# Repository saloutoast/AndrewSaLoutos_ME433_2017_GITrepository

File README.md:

Andrew SaLoutos, 3/28/2017

This repository contains my assignments and project progress for the ME 433 course.

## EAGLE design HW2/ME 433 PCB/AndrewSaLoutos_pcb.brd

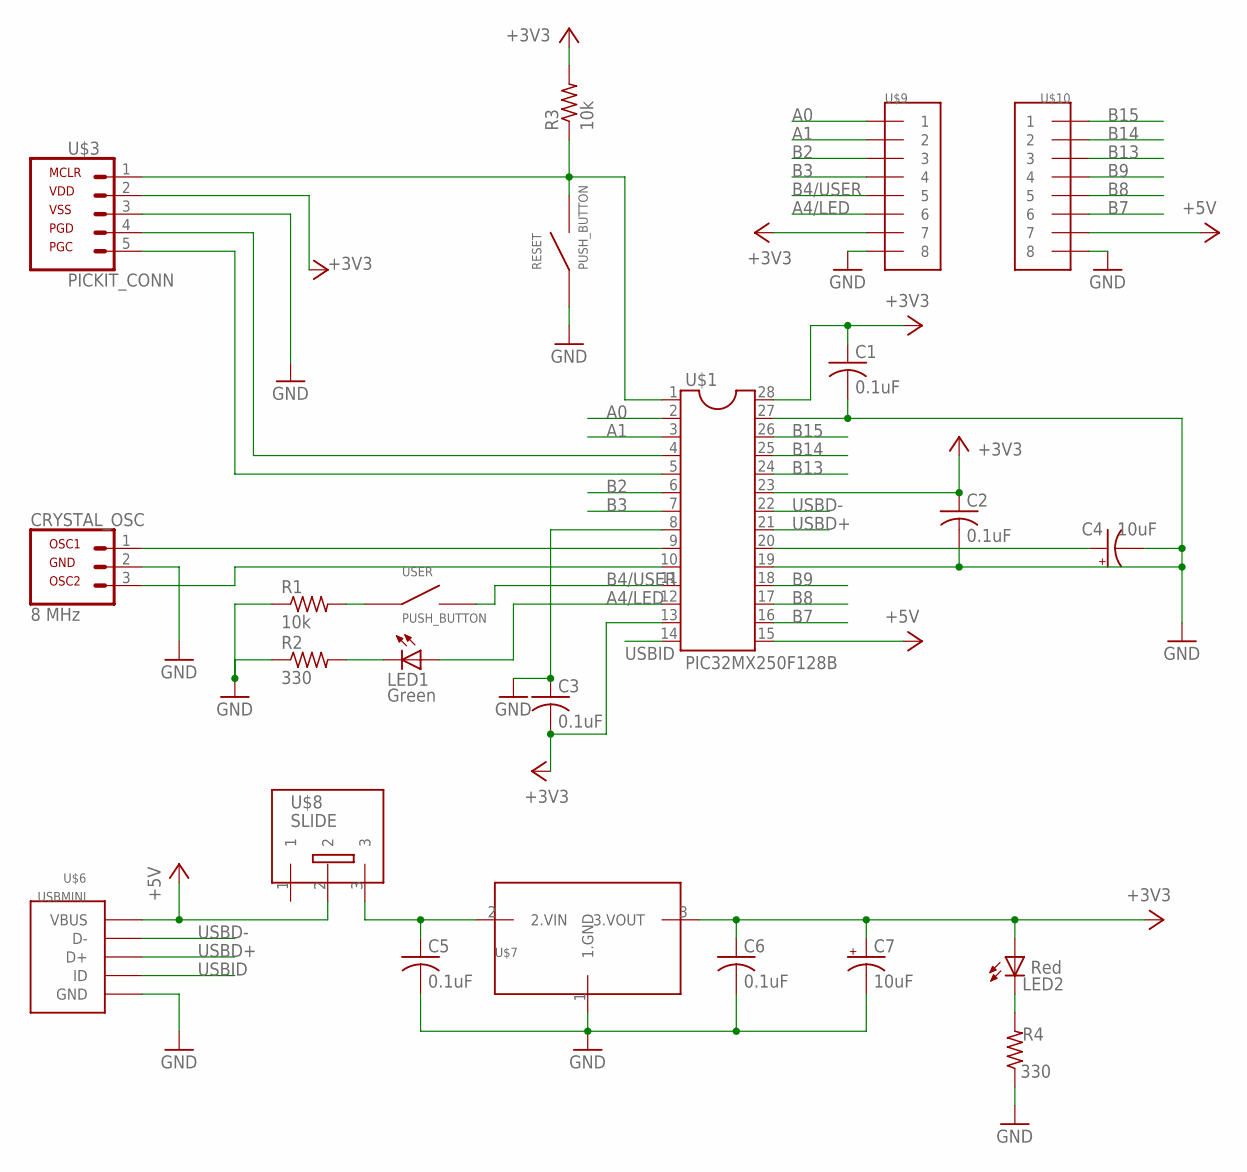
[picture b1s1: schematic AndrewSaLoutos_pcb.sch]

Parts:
C1, C2, C3, C5, C6: 0.1uF; C050-030X075
C4, C7: 10uF; E2,5-6
CRYSTAL_OSC: 8 MHz; 1X03
LED1: Green; LED3MM
LED2: Red; LED3MM
R1, R3: 10k; 0207/10
R2, R4: 330; 0207/10
RESET: PUSH_BUTTON
U$1: PIC32MX250F128B; DIL28-3
U$3: PICKIT_CONN; 1X05
U$6: USBMINI; USB-MB-H
U$7: MCP1702; TO92
U$8: SLIDE
U$9, U$10: 8PIN_HEADER
USER: PUSH_BUTTON

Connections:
+3V3: C1.1, C2.1, C3.2, C6.1, C7.+, LED2.A, R3.2, U$1.13 (13.VDD), U$1.23 (23.VUSB3.3), U$1.28 (28.AVDD), U$3.2 (2.VDD), U$7.3 (3.VOUT), U$9.7
+5V: U$1.15 (15.VBUS), U$6.VBUS, U$8.2, U$10.7
A0: U$1.2, U$9.1
A1: U$1.3, U$9.2
A4/LED: LED1.A, U$1.12 (12.RA4), U$9.6
B2: U$1.6, U$9.3
B3: U$1.7, U$9.4
B4/USER: U$1.11 (11.RB4), U$9.5, USER.3 (OUT)
B7: U$1.16, U$10.6
B8: U$1.17, U$10.5
B9: U$1.18, U$10.4
B13: U$1.24, U$10.3
B14: U$1.25, U$10.2
B15: U$1.26, U$10.1
GND: C1.2, C2.2, C3.1, C4.-, C5.2, C6.2, C7.-, CRYSTAL_OSC.2 (2.GND), R1.1, R2.1, R4.1, RESET.1 (IN), U$1.8 (8.VSS), U$1.19 (19.VSS), U$1.27 (27.AVSS), U$3.3 (3.VSS), U$6.GND, U$7.1 (1.GND), U$9.8, U$10.8
unnamed: C4.+, U$1.20 (20.VCAP)
unnamed: CRYSTAL_OSC.1 (1.OSC1), U$1.9 (9.OSC1)
unnamed: CRYSTAL_OSC.3 (3.OSC2), U$1.10 (10.OSC2)
unnamed: R1.2, USER.1 (IN)
unnamed: LED1.K (C), R2.2
unnamed: U$1.5 (5.PGEC1), U$3.5 (5.PGC)
unnamed: U$1.4 (4.PGED1), U$3.4 (4.PGD)
unnamed: R3.1, RESET.3 (OUT), U$1.1 (1.MCLR), U$3.1 (1.MCLR)
unnamed: C5.1, U$7.2 (2.VIN), U$8.3
unnamed: LED2.K (C), R4.2
USBD+: U$1.21, U$6.D+
USBD-: U$1.22, U$6.D-
USBID: U$1.14, U$6.ID

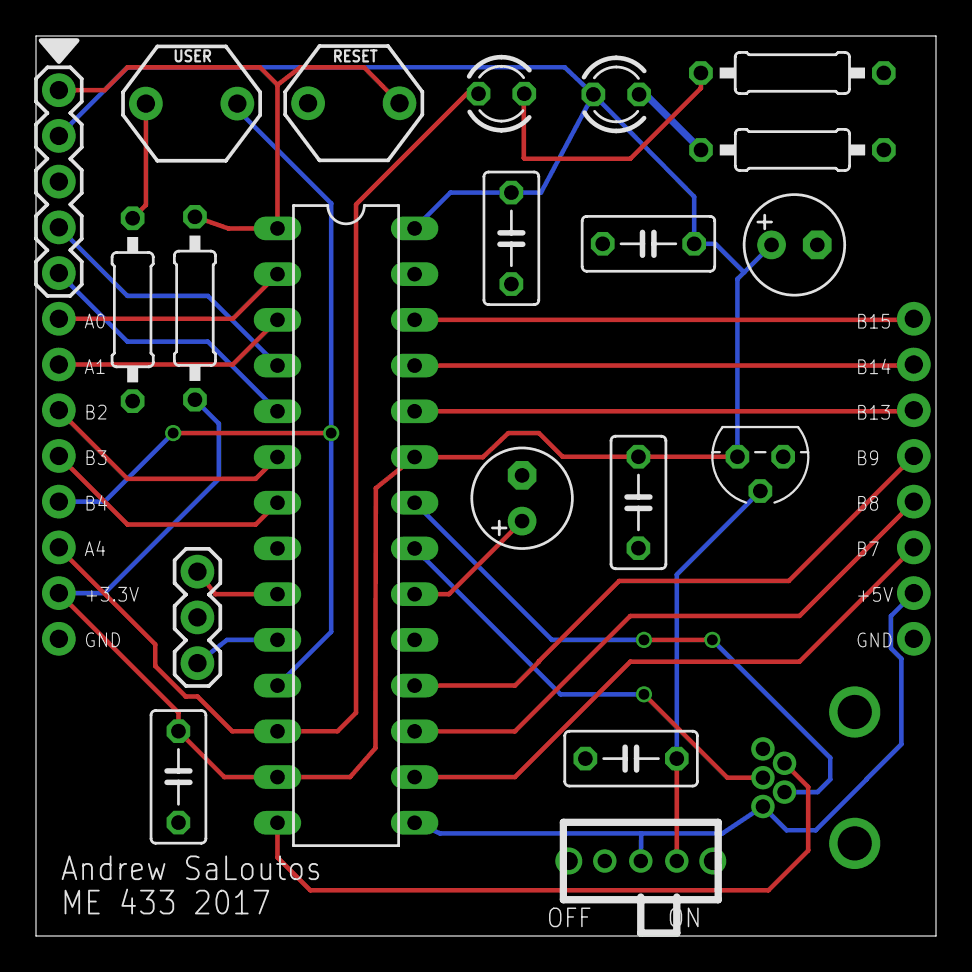
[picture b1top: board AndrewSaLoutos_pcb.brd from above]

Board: 2 copper layers, 50.0 x 50.0 mm, 23 parts (0 on the bottom side), 28 nets.

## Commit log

2017-03-28 My first commit!
2017-03-28 Added one line
2017-03-29 Built the voltage regulator circuit
2017-03-29 Complete circuit diagram
2017-03-29 Complete circuit
2017-03-29 Start of coding for HW1
2017-03-29 pragma values completed
2017-03-29 Toggle green LED, first attempt
2017-03-29 Toggle green LED, second attempt
2017-03-29 Just turn on green LED from PIC
2017-03-29 Toggle green LED, third attempt
2017-03-29 Successful toggle green LED at 50% at ~1 kHz
2017-03-29 push button pause, first attempt
2017-03-29 push button pause, second attempt
2017-03-29 Successful push button pause and restart LED toggling
2017-03-29 Push button and 1 kHz square wave demo video
2017-03-30 Started PCB design, finished creating the library
2017-04-03 Finished the schematic, started the board
2017-04-04 Actually, not quite done with the schematic
2017-04-04 Actually finished schematic, started board layout
2017-04-04 Making progress on board layout
2017-04-04 Everything on the board, not very neat yet
2017-04-04 Ground plane
2017-04-04 Started traces
2017-04-04 More traces
2017-04-04 Traces finished
2017-04-04 DRC checked with Seeed dru from master repository
2017-04-05 Finished board layout, added silkscreen text
2017-04-05 Rotated LED
2017-04-05 Gerber files generated and checked with Mayhew website, HW3 folder created
2017-04-05 Copied board file to HW3 folder
2017-04-10 Started HW4 code with SPI library
2017-04-10 Ready to test spi library
2017-04-10 While loop to test setVoltage function
2017-04-10 Deleted library attempt, square wave from DAC
2017-04-10 Debugging triangle wave, sine wave
2017-04-10 Triangle wave is still buggy, sine does not work
    Triangle wave from output A does not go above half voltage, output from
    B will only do triangle without trouble...it will not even stay high or
    low...will investigate the setVoltage function further tomorrow
2017-04-10 Triangle wave works on both Vout pins from DAC
2017-04-10 sin_track loop tested
2017-04-10 10 Hz sine, 5 Hz triangle outputs work
2017-04-10 Pictures of scope, circuit diagram for HW4
2017-04-11 Demo video
2017-04-12 Started HW5, copied I2C functions from github
2017-04-12 Added semicolon
2017-04-12 Added library for expander functions
2017-04-12 Working on expander functions
2017-04-12 Completed initExpander function
2017-04-12 Finished expander library
2017-04-13 Testing code
2017-04-13 LED blinking successfully when button is pressed
2017-04-13 Demo vid and circuit diagram
2017-04-14 Started HW6 project
2017-04-14 LCD library
2017-04-14 Started main function
2017-04-14 Starting char, string, bar functions
2017-04-14 Tested communication with screen
2017-04-14 Testing displaying one char
2017-04-14 Testing function
2017-04-14 Bar and string functions work
2017-04-14 Final code
2017-04-14 Now the code is final
2017-04-14 Circuit diagram and demo vid
2017-04-20 Testing communication with IMU
2017-04-20 who am i test succeeded
2017-04-20 Bars work, after making array unsigned
2017-04-20 Code complete
2017-04-21 need to remove spaces from file paths for harmony to compile
2017-04-22 Reinstalled MPLAB
    Harmony projects still won't build in Github repository, I'm going to
    build them in the harmony apps folder (where they build successfully)
    and then copy to repository when they are complete
2017-04-22 Copied HW1 and HW7 from harmony directory
2017-04-22 Demo video for harmony version of HW7
2017-04-27 HW9 complete
    only one commit since I have to work out of the /apps folder in the
    harmony filepath to get the project to compile correctly
2017-04-27 Now HW9 is done
2017-05-06 Completed HW12
2017-05-08 HW11 started, mouse moves in circles successfully
2017-05-08 Cannot get readings from IMU
    Re-uploaded HW9, and all values coming from the IMU are 0 even after
    multiple resets...not sure what is going on
2017-05-08 Completed HW11 with demo vid
    Had to unplug, replug, then press reset on PIC to get IMU data to work
    correctly
2017-05-09 Implemented all three filters, no optimization yet
2017-05-09 HW10 complete
2017-05-14 Modifying HW 13
2017-05-14 HW13 completed, added buttons to select filtering color
2017-05-14 HW14 android and PIC code completed
2017-05-16 Demo videos added
2017-05-19 HW 15-17 completed
2017-05-29 started HW18
2017-05-30 final android app with two sliders
2017-05-30 first test with phone
2017-05-30 Can send values
    Can send values to both motors with two sliders
2017-05-30 app crashes with camera code
2017-05-30 camera and usb work, not interfaced yet
2017-05-30 pic of map
2017-05-30 split image into two halves for motor control
2017-05-30 changed some text
2017-05-30 need to test control
2017-06-04 one changed
2017-06-04 close down
2017-06-05 Follows the line sometimes
2017-06-06 switching control methods soon
    last try with control through difference of com_near and com_far
2017-06-06 new control
    two gains and error bounds for near and far CoMs
2017-06-06 lower base speed, only far pixels
2017-06-06 IT WORKS FUCK YEAH
2017-06-06 starting to work on the vive and servo
2017-06-06 basic servo and vive functionality
2017-06-07 comments for servo and vive
2017-06-07 small wheels work well, moving to large wheels
2017-06-07 last try for big wheels params?
2017-06-07 one last try
2017-06-07 one last shot
2017-06-07 back to small wheels for final demo
2017-06-07 it works!!!! (again)
2017-06-09 Final demo code
